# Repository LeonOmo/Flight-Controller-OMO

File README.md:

# Flight-Controller-OMO

A custom designed, minimalistic STM32F411-based flight controller built from scratch for custom drone and aerospace experimentation.

## What is this project?

Flight Controller OMO: is a custom made circuit board designed specifically to act as an stabilization unit for stabilising platforms. It breaks away from bulky flight controllers by packing only the essential, minimal form factor powered by an STM32 microcontroller and a modern BMI270.

## Purpose & What it does

The primary purpose of this board is to process real-time orientation data and translate pilot control inputs into precise motor commands. 
- Attitude: Reads high speed gyro and accelerometer data via the BMI270 sensor to keep the aircraft stable.
- Motor Control: Provides 4 dedicated motor output attachments to drive electronic speed controllers (ESCs) or micro motors.
- Firmware: Designed to run standard flight controller firmware like Betaflight.
- Flashing: Includes a 12 pin USB-C interface for seamless connection to a PC for configuration and flashing.

## Why does it exist?

Building an off the shelf drone is fun, but designing the core avionics from the ground up teaches you how hardware, firmware, and circuit layout actually interact in the real world. 

- The Learning Curve: Moving away from older, obsolete sensors like the MPU6050 to the modern BMI270 was a major step in modernizing the design.
- Aerospace Passion: As a personal stepping stone for aerospace and rocketry drone payloads having total control over a custom flight controller design opens up endless possibilities for tailored form factors.
- Just for Fun: Pure engineering curiosity testing whether a self routed PCB built in KiCAD can successfully boot, communicate, and stabilize a flight platform. (As of now, it's a first prototype fingers crossed that everything works as intended!)

## Bill of Materials

| Designator | Component | Footprint | LCSC Part Number | Description |
| :--- | :--- | :--- | :--- | :--- |
| U2 | STM32F411CEU6 | QFN-48 (7x7mm) | C60420 | Main MCU |
| U4 | BMI270 | 14-LGA (3x2.5mm) | C2836813 | Gyro + Accel |
| U3 | ME6211C33M5G-N | SOT-23-5 | C82942 | 3.3V Voltage Regulator |
| J1 | USB4105-GF-A-120 | USB-C 16-Pin SMT | C5184243 | USB-C Receptacle |
| Y1 | 16MHz Crystal | SMD 3225-4P | C13738 | Crystal Oscillator |
| C5, C6 | 10µF | 0603 (1608 Metric) | C19702 | Ceramic Capacitor |
| C7 | 2.2µF | 0603 (1608 Metric) | C23630 | Ceramic Capacitor |
| D1, D2 | LED | 0603 (1608 Metric) | C2290 | Status / Power LEDs |
| R3 | 1MΩ | 0603 (1608 Metric) | C22935 | Resistor |
| R4, R5 | 5.1kΩ | 0603 (1608 Metric) | C23186 | USB-C Resistors |
| R6, R7 | 10kΩ | 0603 (1608 Metric) | C25804 | Config Resistors |
| R8, R9 | 1kΩ | 0603 (1608 Metric) | C21190 | LED Current Limiting Resistors |

## Tools & Technologies

- PCB Design: KiCAD
- Firmware: Betaflight
- Design Highlights: Features a custom silkscreen layout including things like Mewo.

## Schematics & PCB Layout

## Schematic

## PCB

## Extras

I liked this way more than id like to admit making this was really fun for me and it was just so freeing.

## Bonus

Before settling on the BMI270, early iterations used the older MPU6050. Transitioning away from it was a major hurdle due to its age and lack of modern integration support, making the shift to the BMI270 a much cleaner and more reliable choice for modern layouts.

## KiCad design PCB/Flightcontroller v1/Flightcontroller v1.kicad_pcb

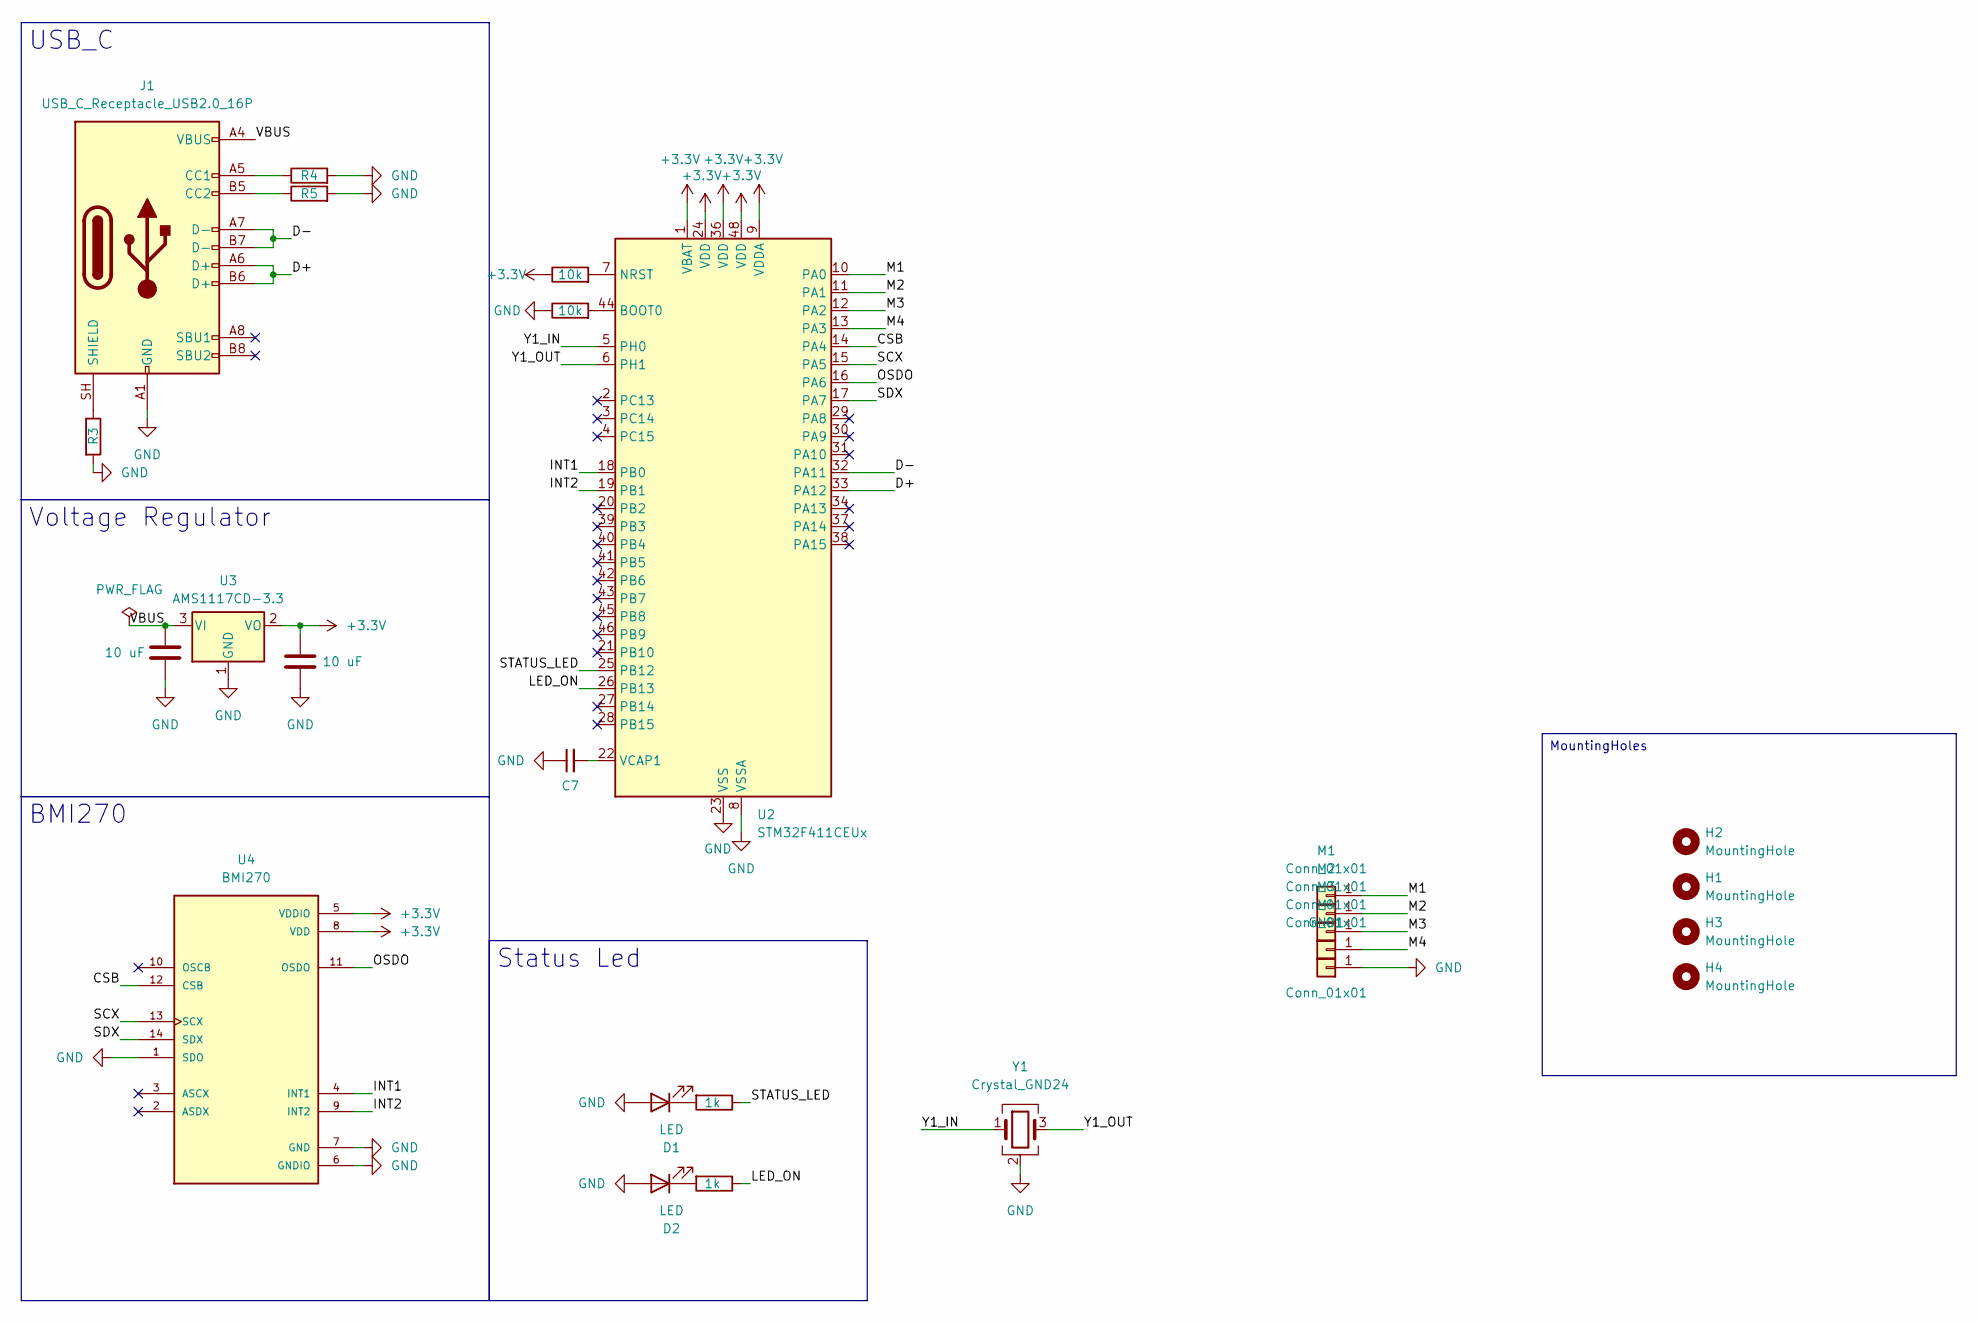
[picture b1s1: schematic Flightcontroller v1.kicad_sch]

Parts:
C5, C6: 10 uF; C_0603_1608Metric
C7: 2.2uF; C_0603_1608Metric
D1, D2: LED; LED_0603_1608Metric
GND1: Conn_01x01; TestPoint_Pad_D1.5mm
H1, H2, H3, H4: MountingHole; MountingHole_3.2mm_M3
J1: USB_C_Receptacle_USB2.0_16P; USB_C_Receptacle_GCT_USB4105-xx-A_16P_TopMnt_Horizontal
M1, M2, M3, M4: Conn_01x01; TestPoint_Pad_D1.5mm
R3: 1M; R_0603_1608Metric
R4, R5: 5.1k; R_0603_1608Metric
R6, R7: 10k; R_0603_1608Metric
R8, R9: 1k; R_0603_1608Metric
U2: STM32F411CEUx; QFN-48-1EP_7x7mm_P0.5mm_EP5.6x5.6mm
U3: AMS1117CD-3.3; SOT-23-5
U4: BMI270; XDCR_BMI270
Y1: Crystal_GND24; Crystal_SMD_3225-4Pin_3.2x2.5mm

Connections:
+3.3V: C5.1, R6.1, U2.1 (VBAT), U2.9 (VDDA), U2.24 (VDD), U2.36 (VDD), U2.48 (VDD), U3.2 (VO), U4.5 (VDDIO), U4.8 (VDD)
/CSB: U2.14 (PA4), U4.12 (CSB)
/D+: J1.A6 (D+), J1.B6 (D+), U2.33 (PA12)
/D-: J1.A7 (D-), J1.B7 (D-), U2.32 (PA11)
/INT1: U2.18 (PB0), U4.4 (INT1)
/INT2: U2.19 (PB1), U4.9 (INT2)
/LED_ON: R9.1, U2.26 (PB13)
/M1: M1.1 (Pin_1_1), U2.10 (PA0)
/M2: M2.1 (Pin_1_1), U2.11 (PA1)
/M3: M3.1 (Pin_1_1), U2.12 (PA2)
/M4: M4.1 (Pin_1_1), U2.13 (PA3)
/OSDO: U2.16 (PA6), U4.11 (OSDO)
/SCX: U2.15 (PA5), U4.13 (SCX)
/SDX: U2.17 (PA7), U4.14 (SDX)
/STATUS_LED: R8.1, U2.25 (PB12)
/VBUS: C6.1, J1.A4 (VBUS), J1.A9 (VBUS), J1.B4 (VBUS), J1.B9 (VBUS), U3.3 (VI)
/Y1_IN: U2.5 (PH0), Y1.1
/Y1_OUT: U2.6 (PH1), Y1.3
GND: C5.2, C6.2, C7.1, D1.2 (A), D2.2 (A), GND1.1 (Pin_1_1), J1.A1 (GND), J1.A12 (GND), J1.B1 (GND), J1.B12 (GND), R3.2, R4.2, R5.2, R7.1, U2.8 (VSSA), U2.23 (VSS), U2.35 (VSS), U2.47 (VSS), U2.49 (VSS), U3.1 (GND), U4.1 (SDO), U4.6 (GNDIO), U4.7 (GND), Y1.2 (G), Y1.4 (G)
unnamed: D1.1 (K), R8.2
unnamed: D2.1 (K), R9.2
unnamed: J1.A5 (CC1), R4.1
unnamed: J1.B5 (CC2), R5.1
unnamed: J1.SH (SHIELD), R3.1
unnamed: R7.2, U2.44 (BOOT0)
unnamed: R6.2, U2.7 (NRST)
unnamed: C7.2, U2.22 (VCAP1)

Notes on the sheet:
MountingHoles
USB_C
Voltage Regulator
Status Led
BMI270

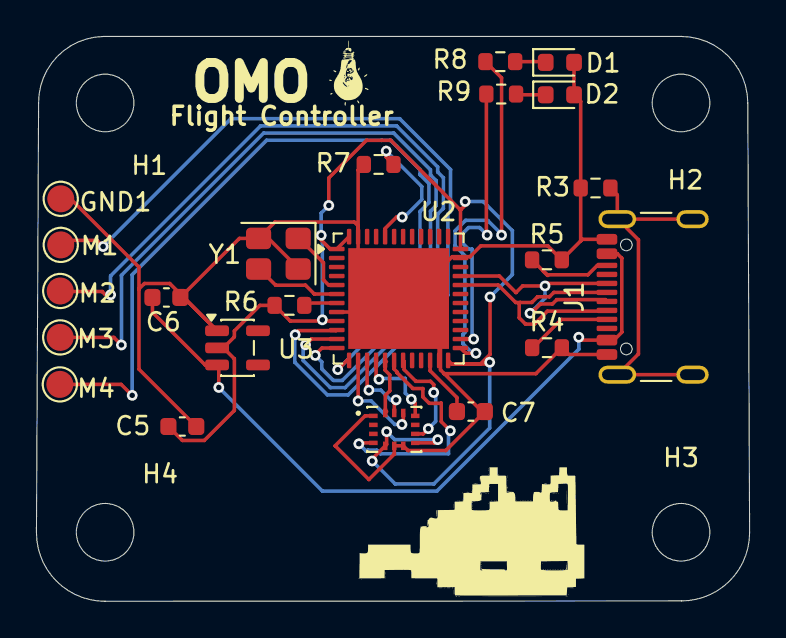
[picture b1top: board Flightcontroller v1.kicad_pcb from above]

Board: 2 copper layers, 39.6 x 31.4 mm, 26 parts (0 on the bottom side), 27 nets.

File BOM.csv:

Designator,Component / Value,Footprint / Package,LCSC Part Number,Description / Notes
U2,STM32F411CEU6,QFN-48 (7x7mm),C60420,Main MCU (100MHz, 512KB Flash)
U4,BMI270,14-LGA (3x2.5mm),C2836813,6-Axis IMU (Gyro + Accel) via SPI
U3,ME6211C33M5G-N,SOT-23-5,C82942,3.3V LDO Voltage Regulator (500mA)
J1,USB4105-GF-A-120,USB-C 16-Pin SMT,C5184243,USB-C Receptacle (USB 2.0)
Y1,16MHz Crystal,SMD 3225-4P,C13738,HSE Crystal Oscillator (9pF)
C5, C6,10µF,0603 (1608 Metric),C19702,Ceramic Capacitor (10V, X5R)
C7,2.2µF,0603 (1608 Metric),C23630,Ceramic Capacitor (16V, X5R)
D1, D2,LED,0603 (1608 Metric),C2290,Status / Power LEDs
R3,1MΩ,0603 (1608 Metric),C22935,Resistor (ESD Shield GND)
R4, R5,5.1kΩ,0603 (1608 Metric),C23186,USB-C CC1/CC2 Pull-down Resistors
R6, R7,10kΩ,0603 (1608 Metric),C25804,Pull-up / Config Resistors
R8, R9,1kΩ,0603 (1608 Metric),C21190,LED Current Limiting Resistors
